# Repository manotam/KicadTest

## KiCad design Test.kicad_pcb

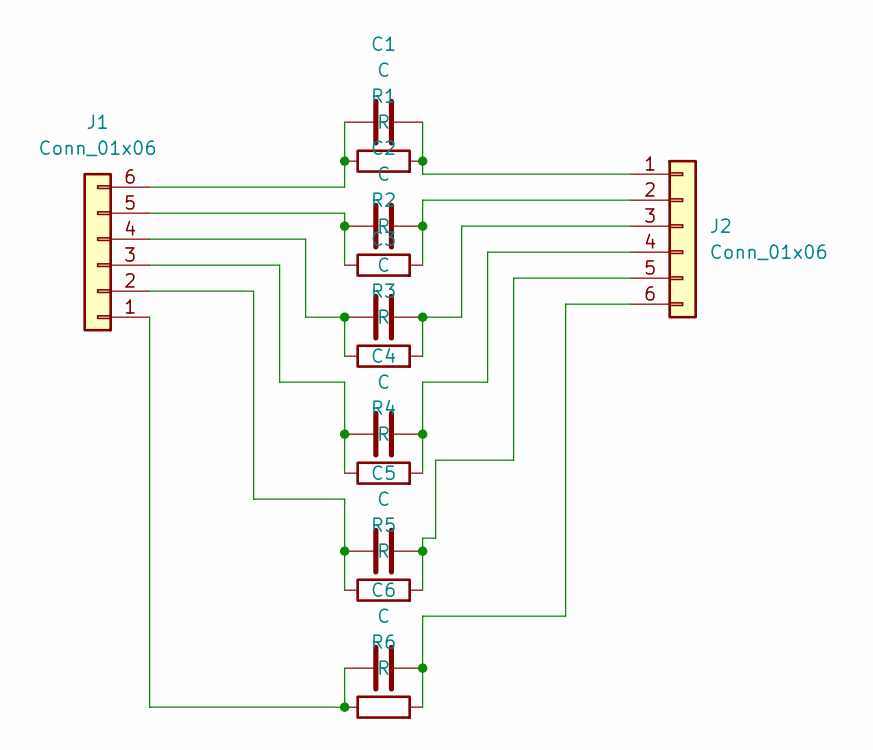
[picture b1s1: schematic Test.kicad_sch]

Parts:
C1, C2, C3, C4, C5, C6: C; C_0805_2012Metric
J1, J2: Conn_01x06; PinHeader_1x06_P2.54mm_Vertical
R1, R2, R3, R4, R5, R6: R; R_0805_2012Metric

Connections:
unnamed: C1.1, J1.6, R1.1
unnamed: C1.2, J2.1, R1.2
unnamed: C2.1, J1.5, R2.1
unnamed: C2.2, J2.2, R2.2
unnamed: C3.1, J1.4, R3.1
unnamed: C3.2, J2.3, R3.2
unnamed: C4.1, J1.3, R4.1
unnamed: C4.2, J2.4, R4.2
unnamed: C5.1, J1.2, R5.1
unnamed: C5.2, J2.5, R5.2
unnamed: C6.1, J1.1, R6.1
unnamed: C6.2, J2.6, R6.2

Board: 2 copper layers, 14 parts (0 on the bottom side), 12 nets, no tracks yet.
